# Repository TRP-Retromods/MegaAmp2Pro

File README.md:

# Mega Amp 2.0 Pro
Original design by Ace and Villahed94

What makes the Mega Amp 2.0 different from the original design?
Due to limitations of the chosen op-amps on the original Mega Amp, volume levels are limited to those of every Genesis made from the VA0 Genesis Model 2 onwards. With new components chosen for the Mega Amp 2.0, you can now blow your ears out with sound even louder than the loudest Genesis Model 1s.
Every Genesis will now be able to drive headphones, as well. The transistor buffers from the original design are gone, replaced by a TDA1308, a dual op-amp with a built-in headphone driver. It is this chip that is able to bring the higher volume and also simplify the design by integrating a superior headphone driver.
The Mega Amp 2.0 retains the 3.68KHz low-pass filtering for Genesis Model 1-like audio on the filtered setup, but the unfiltered setup now goes beyond the audible spectrum, filtering frequencies past 24.56KHz for the clearest sound possible.

This is the big one, the full-featured Mega Amp 2.0. It has it all: multiple different filter setups, Stereo and Mono audio, AND the added bonus of Sega CD audio mixing (Sega CD Model 2 or modded Sega CD Model 1 required to take advantage of this). Anyone who owns a Sega CD can choose what kind of audio they want out of their Genesis and Sega CD.

To sum up the Mega Amp 2.0:
-An even simpler design over the original Mega Amp (excluding the Mega Amp 2.0 Pro)
-Filtered circuits deliver the same sound as a VA0 to VA2 Genesis Model 1 minus distortion
-Unfiltered circuits deliver the full spectrum of the Genesis' audio output
-The loudest audio levels of any audio amp for the Genesis, including Sega’s amp for the VA3 Genesis Model 1
-Improved headphone support
-Sega CD pass-through for the Mega Amp 2.0 Pro for a true replacement audio circuit with no loss in functionality
-Mega Amp 2.0 Pro can add Sega CD pass-through to the Genesis Model 1

Sega-16 forums are downs, so I compile all explanation and installation in this doc: https://github.com/TRP-Retromods/MegaAmp2Pro/blob/master/MEGAAMP_2_DOC+INSTALL_V1.pdf

Quick Guide to help soldering the components on the PCB: https://github.com/TRP-Retromods/MegaAmp2Pro/blob/master/MEGAMP_2_PRO_QUICK_GUIDE_V3.pdf

Boards can be ordered on OSHPark https://oshpark.com/shared_projects/v1SMwG5q

https://youtu.be/V17gc4aD0Z8

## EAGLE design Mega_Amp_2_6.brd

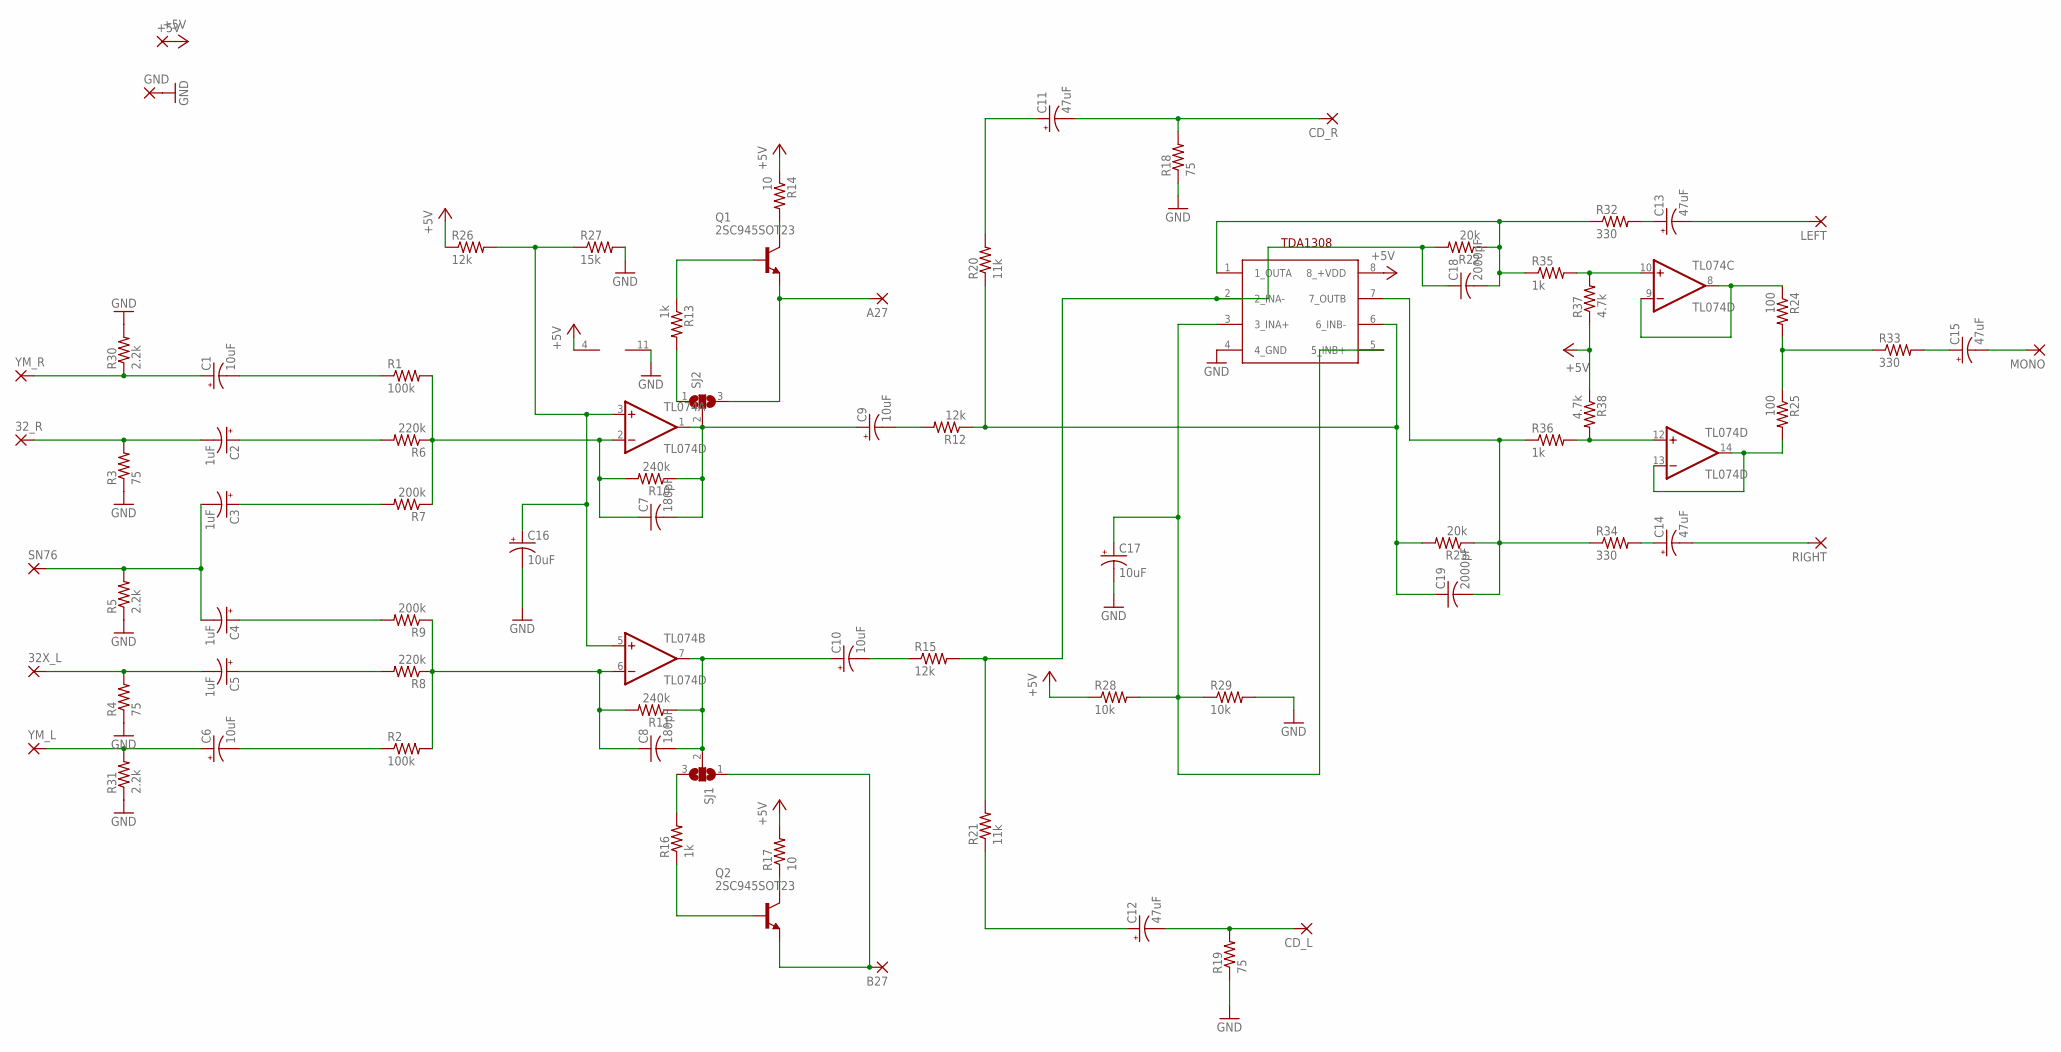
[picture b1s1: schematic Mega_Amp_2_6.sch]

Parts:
32X_L, 32_R: SMD2; SMD1,27-2,54
+5V: SMD5; SMD2,54-5,08
A27: SMD2; SMD1,27-2,54
B27: SMD2; SMD1,27-2,54
C1, C6, C9, C10, C16, C17: 10uF; 153CLV-0405
C2, C3, C4, C5: 1uF; 153CLV-0405
C7, C8: 180pF; C0603
C11, C12, C13, C14, C15: 47uF; 153CLV-0505
C18, C19: 2000pF; C0603
CD_L: SMD2; SMD1,27-2,54
CD_R: SMD2; SMD1,27-2,54
GND: SMD5; SMD2,54-5,08
LEFT: SMD2; SMD1,27-2,54
MONO: SMD2; SMD1,27-2,54
Q1, Q2: 2SC945SOT23; SOT23
R1, R2: 100k; R0603
R3, R4, R18, R19: 75; R0603
R5, R30, R31: 2.2k; R0603
R6, R8: 220k; R0603
R7, R9: 200k; R0603
R10, R11: 240k; R0603
R12, R15, R26: 12k; R0603
R13, R16, R35, R36: 1k; R0603
R14, R17: 10; R0603
R20, R21: 11k; R0603
R22, R23: 20k; R0603
R24, R25: 100; R0603
R27: 15k; R0603
R28, R29: 10k; R0603
R32, R33, R34: 330; R0603
R37, R38: 4.7k; R0603
RIGHT: SMD2; SMD1,27-2,54
SJ1, SJ2: SJ2W; SJ_2
SN76: SMD2; SMD1,27-2,54
TDA1308: TDA1308SO8; SO8
TL074: TL074D; SO14
YM_L: SMD2; SMD1,27-2,54
YM_R: SMD2; SMD1,27-2,54

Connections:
+5V: +5V.1, R14.1, R17.2, R26.1, R28.1, R37.1, R38.1, TDA1308.8 (8_+VDD), TL074.4 (V+)
GND: C16.-, C17.-, GND.1, R3.1, R4.1, R5.1, R18.1, R19.1, R27.2, R29.2, R30.2, R31.1, TDA1308.4 (4_GND), TL074.11 (V-)
unnamed: C1.+, R30.1, YM_R.1
unnamed: C1.-, R1.1
unnamed: 32_R.1, C2.-, R3.2
unnamed: C2.+, R6.2
unnamed: C3.-, C4.-, R5.2, SN76.1
unnamed: C3.+, R7.2
unnamed: C4.+, R9.2
unnamed: C7.1, R1.2, R6.1, R7.1, R10.2, TL074.2 (-IN)
unnamed: C8.1, R2.2, R8.1, R9.1, R11.2, TL074.6 (-IN)
unnamed: C5.+, R8.2
unnamed: C6.-, R2.1
unnamed: 32X_L.1, C5.-, R4.2
unnamed: C6.+, R31.2, YM_L.1
unnamed: C16.+, R26.2, R27.1, TL074.3 (+IN), TL074.5 (+IN)
unnamed: C7.2, C9.+, R10.1, SJ2.2, TL074.1 (OUT)
unnamed: Q1.1 (B), R13.1
unnamed: C8.2, C10.+, R11.1, SJ1.2, TL074.7 (OUT)
unnamed: Q1.3 (C), R14.2
unnamed: A27.1, Q1.2 (E), SJ2.3
unnamed: C9.-, R12.2
unnamed: C19.1, R12.1, R20.1, R23.2, TDA1308.6 (6_INB-)
unnamed: C11.+, R20.2
unnamed: C11.-, CD_R.1, R18.2
unnamed: C13.-, LEFT.1
unnamed: C15.-, MONO.1
unnamed: R24.2, R25.1, R33.1
unnamed: C10.-, R15.1
unnamed: C17.+, R28.2, R29.1, TDA1308.3 (3_INA+), TDA1308.5 (5_INB+)
unnamed: Q2.1 (B), R16.1
unnamed: Q2.3 (C), R17.1
unnamed: B27.1, Q2.2 (E), SJ1.1
unnamed: C12.+, R21.1
unnamed: C12.-, CD_L.1, R19.2
unnamed: C18.1, R15.2, R21.2, R22.2, TDA1308.2 (2_INA-)
unnamed: R24.1, TL074.8 (OUT), TL074.9 (-IN)
unnamed: R25.2, TL074.13 (-IN), TL074.14 (OUT)
unnamed: C14.-, RIGHT.1
unnamed: C13.+, R32.2
unnamed: C14.+, R34.2
unnamed: C15.+, R33.2
unnamed: R13.2, SJ2.1
unnamed: C19.2, R23.1, R34.1, R36.1, TDA1308.7 (7_OUTB)
unnamed: R16.2, SJ1.3
unnamed: R35.2, R37.2, TL074.10 (+IN)
unnamed: C18.2, R22.1, R32.1, R35.1, TDA1308.1 (1_OUTA)
unnamed: R36.2, R38.2, TL074.12 (+IN)

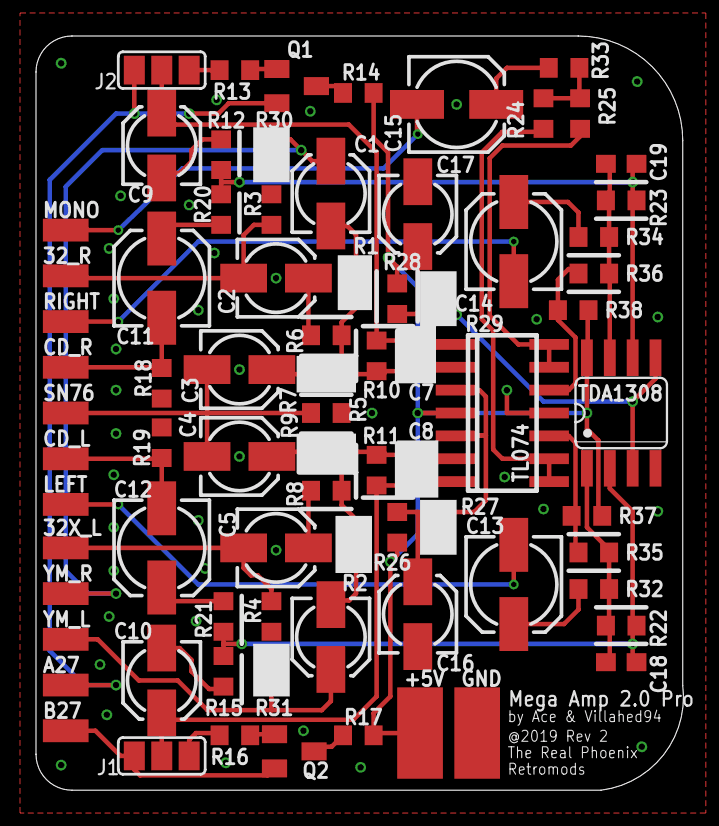
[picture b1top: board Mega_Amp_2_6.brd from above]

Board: 2 copper layers, 36.0 x 41.9 mm, 77 parts (0 on the bottom side), 48 nets.

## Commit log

2019-05-25 Add Rev2 Eagle Files
2019-05-25 Add Gerber files
2019-05-25 Add BOM from Digikey
2019-05-25 update BOM for REV2
2019-08-02 Add files via upload
    Adding capture from the scematics to show differences from original scematics in the Sega16's forum
2023-07-12 Documention
    - Add PDF with compiled version of installation + scematics compiled from SEGA-16 Forum
    - Update PDF for quick install
2023-07-20 update doc
    updated fixed typo
2023-07-20 Update MEGAAMP_2_DOC+INSTALL_V1-1.pdf
    Add A27/B27 section
